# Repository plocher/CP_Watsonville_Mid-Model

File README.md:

# CP_Watsonville_South-Model
## License: CERN Open Hardware Licence v1.2

Model Board for CP Watsonville Middle yard - Maintainer Sevice Panel

Prototype for debugging and remote feedback

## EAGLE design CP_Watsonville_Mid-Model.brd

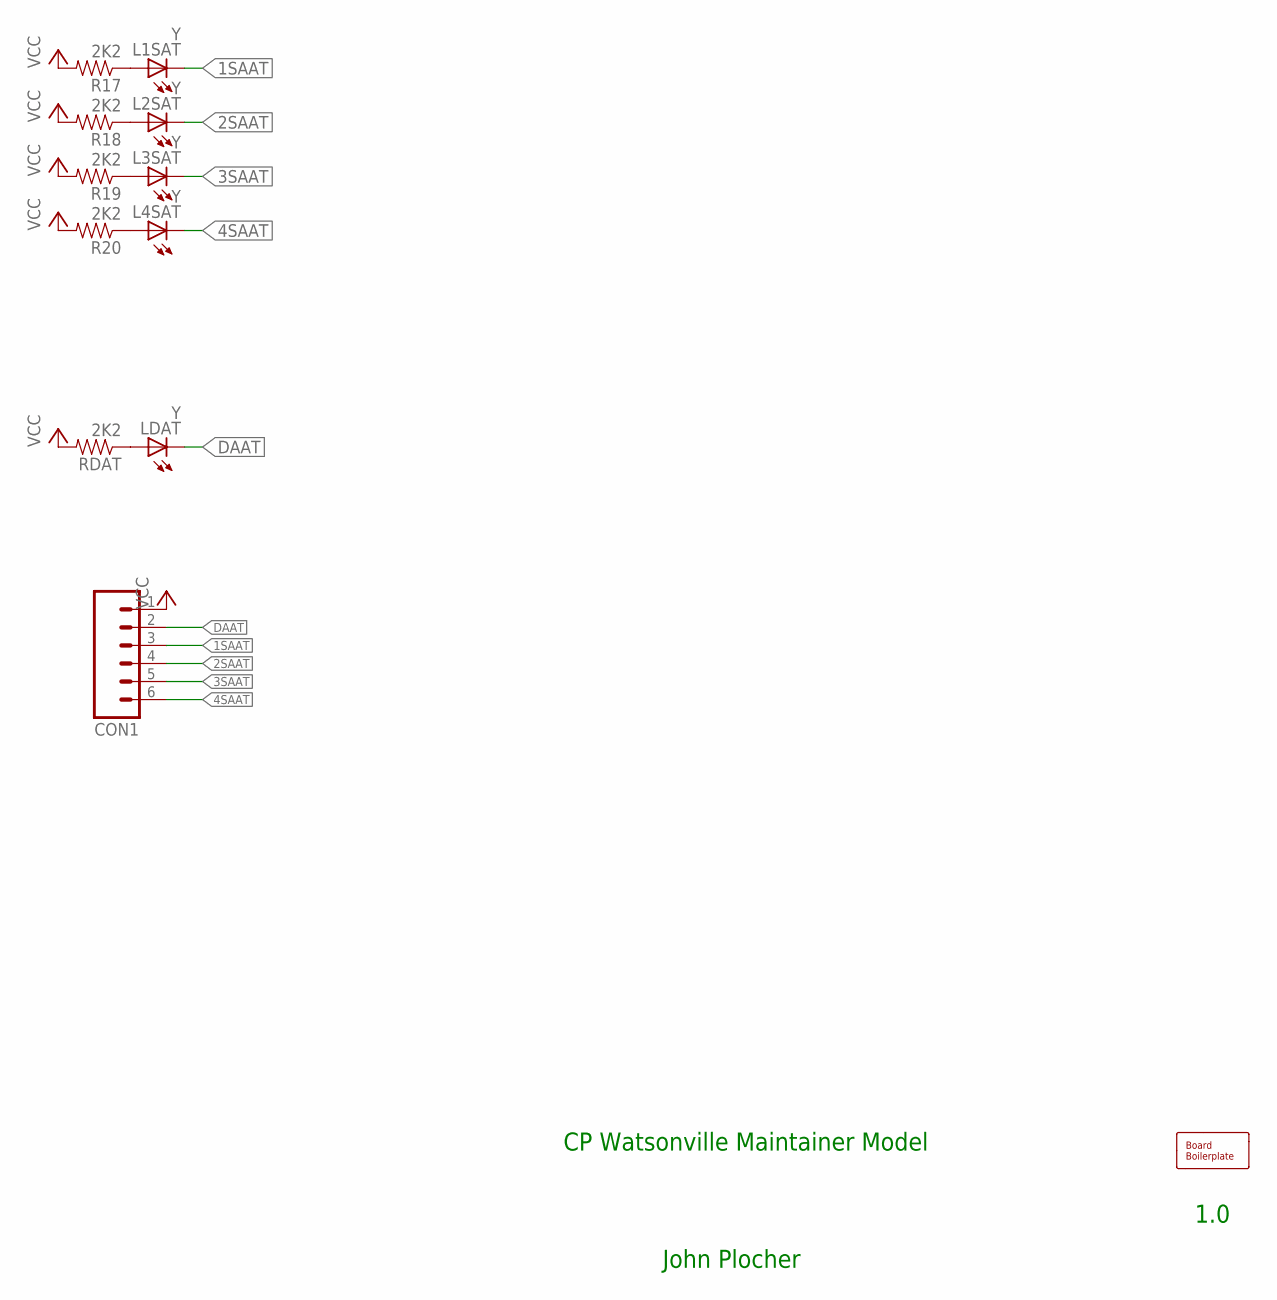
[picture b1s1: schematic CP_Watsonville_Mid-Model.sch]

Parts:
BOARD1: BOARD100X100; BOARD-SEEED10X10
CON1: CONNECTOR-M06LOCK; 1X06_LOCK
L1SAT, L2SAT, L3SAT, L4SAT: Y; 0603-LED
LDAT: Y; 0603-LED
R17, R18, R19, R20: 2K2; 0603-RES
RDAT: 2K2; 0603-RES

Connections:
1SAAT: CON1.3, L1SAT.C
2SAAT: CON1.4, L2SAT.C
3SAAT: CON1.5, L3SAT.C
4SAAT: CON1.6, L4SAT.C
DAAT: CON1.2, LDAT.C
unnamed: LDAT.A, RDAT.1
unnamed: L1SAT.A, R17.1
unnamed: L2SAT.A, R18.1
unnamed: L3SAT.A, R19.1
unnamed: L4SAT.A, R20.1
VCC: CON1.1, R17.2, R18.2, R19.2, R20.2, RDAT.2

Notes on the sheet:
CP Watsonville Maintainer Model
1.0
John Plocher

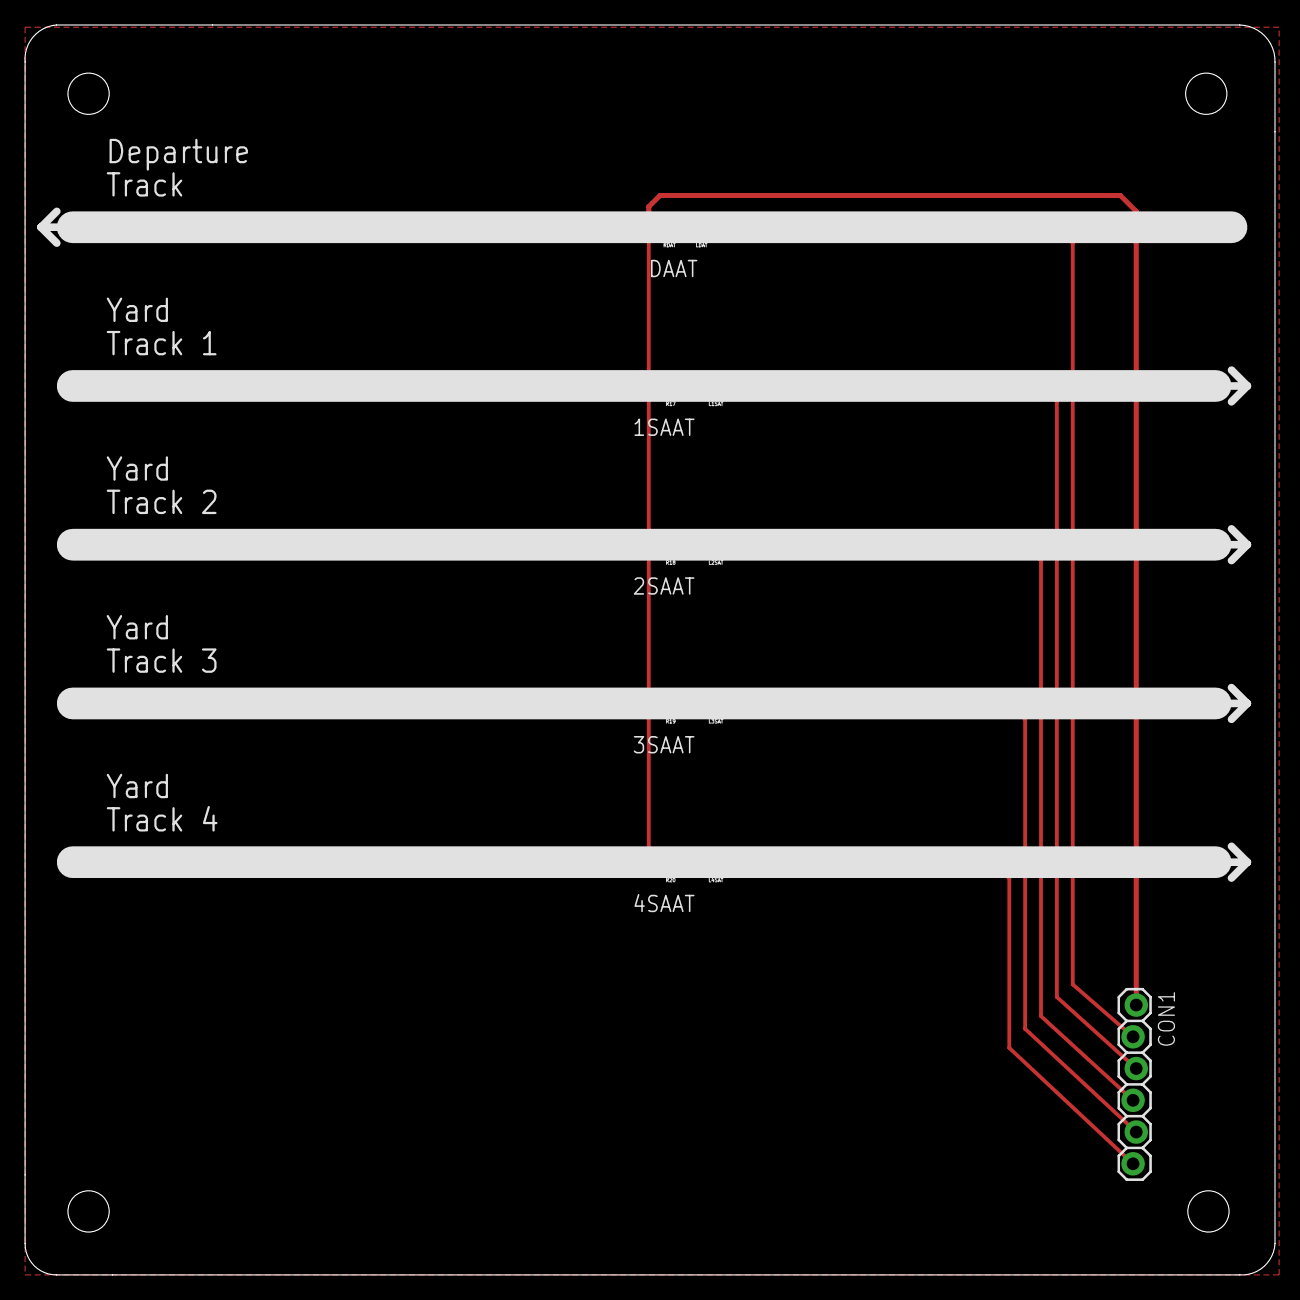
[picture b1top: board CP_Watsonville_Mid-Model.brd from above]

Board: 2 copper layers, 100.0 x 100.0 mm, 12 parts (0 on the bottom side), 11 nets.

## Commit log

2020-11-03 Initial version
2020-11-03 Added 1x6 for MID-model board
2020-11-03 Aligned between boards
2020-11-03 Round corner board
2020-11-03 Added JLC Part number template to back silk
